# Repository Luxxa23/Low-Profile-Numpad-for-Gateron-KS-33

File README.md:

# Low Profile Numpad

for Gateron Low Profile 2.0 (KS-33) switches
Designed to fit in next to a Keychron K3 Max (or their other low profile keyboards)

## Design Process

The numpd was designed to match the outer dimensions of my Keychron K3 Max and use the same hotswap switches. The PCB was designed in [KiCad](https://github.com/KiCad), the case in Autodesk 
Fusion and the plate in [LibreCad](https://github.com/LibreCAD/LibreCAD) and imported into KiCad.
This was my first time designing a PCB, so the design is probably far from optimal. But it works!

Things to improve/do differently:
- Use the switches with a black housing to blend in with the black case
- Use original Keychron keycaps (if they sold them separately...)

## Building Materials

* Gateron [KS-33 Switches ](https://www.gateron.com/products/gateron-ks-33-low-profile-switch-set)
* Gateron [Low Profile Hotswap Sockets](https://www.gateron.com/products/gateron-low-profile-switch-hot-swap-pcb-socket)
* Gateron [Low Profile Stabilizers](https://www.gateron.com/products/gateron-low-profile-plate-mounted-stabilizer?VariantsId=10477)
* Wormier double-shot PBT keycaps [Aliexpress](https://aliexpress.com/item/1005008227731750.html)

* Adafruit [QT Py RP2040](https://www.adafruit.com/product/4900)
* 0.91" OLED Display (SSD1306) [Aliexpress](https://de.aliexpress.com/item/1005004622658983.html)
* Bourns PEC11R-4315F-S0012 [Encoder](https://www2.mouser.com/ProductDetail/652-PEC11R4315FS0012)
* PCBs ordered on [JLCPCB](https://jlcpcb.com/)
* M2 heat set inserts and screws

## Build Notes

* PCBs ordered on [JLCPCB](https://jlcpcb.com/). The main PCB is 1.6mm thick, the plate PCB is 1mm thick.

* The parts were printed on a BambuLab A1 using their black PLA Basic filament.

* The fit of the PCB is pretty tight, maybe it should've been a few millimetres wider. There are holes for M2x3 heat set inserts in the case. I used black M2x8 screws with a flat, non-countersunk head.
* I used a sharpie to paint the edge of the plate PCB black.
* Use thin, flexible wires for the encoder since there's no a lot of space in the case
*The cover for the OLED is only 0.6mm at the top, so it's very flimsy. If you have a smooth build plate print it upside down, I printed it using the top layer ironing feature with supports. The OLED is supposed to slide into the cover from the side. The fit is too tight, so use a small file to get it to fit perfectly.
*There are 11mm diameter, 1.5mm deep holes on the botton where for small rubber feet can be stuck.

## Firmware

Since the numpad is using an RP2040 processor, I decided to use [KMK Firmware](https://github.com/KMKfw/kmk_firmware).
I uploaded my code.py file, you'll have to install and set up KMK yourself (and edit the OLED display contents/make your own images for it)
My programming knowledge is pretty limited and there aren't a lot of resources on KMK online, so I didn't figure out how to get the display to show Num- and Caps lock without using dummy layers as variables.

## Inspiration and resources

Inspiration for plate PCB and distances between keys: https://github.com/shanna/pla_nck

KiCad footprint for Gateron Low Profile hotswap sockets: https://gist.github.com/niw/22c68c2d7c869b990588b4875a654442 

## Gallery

.jpg)

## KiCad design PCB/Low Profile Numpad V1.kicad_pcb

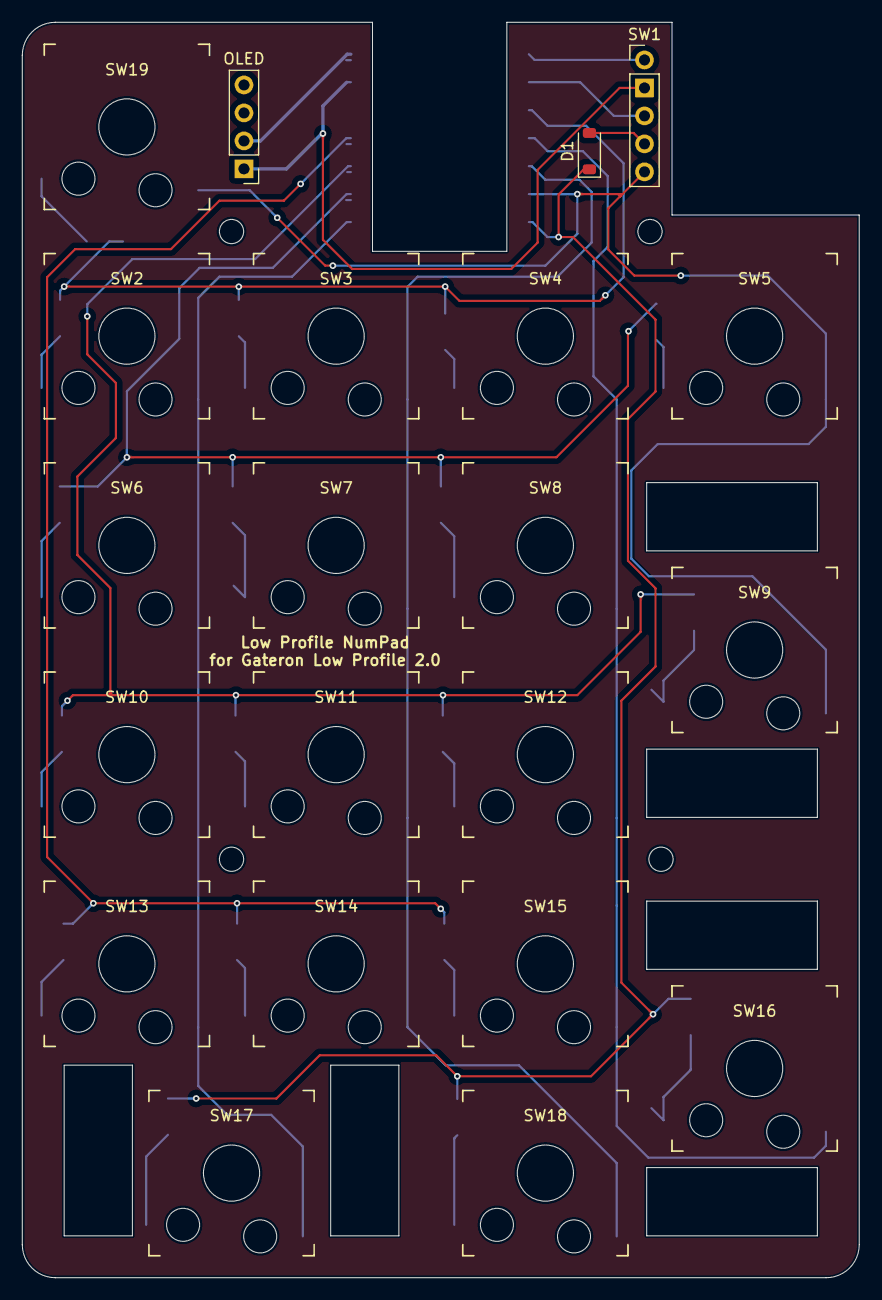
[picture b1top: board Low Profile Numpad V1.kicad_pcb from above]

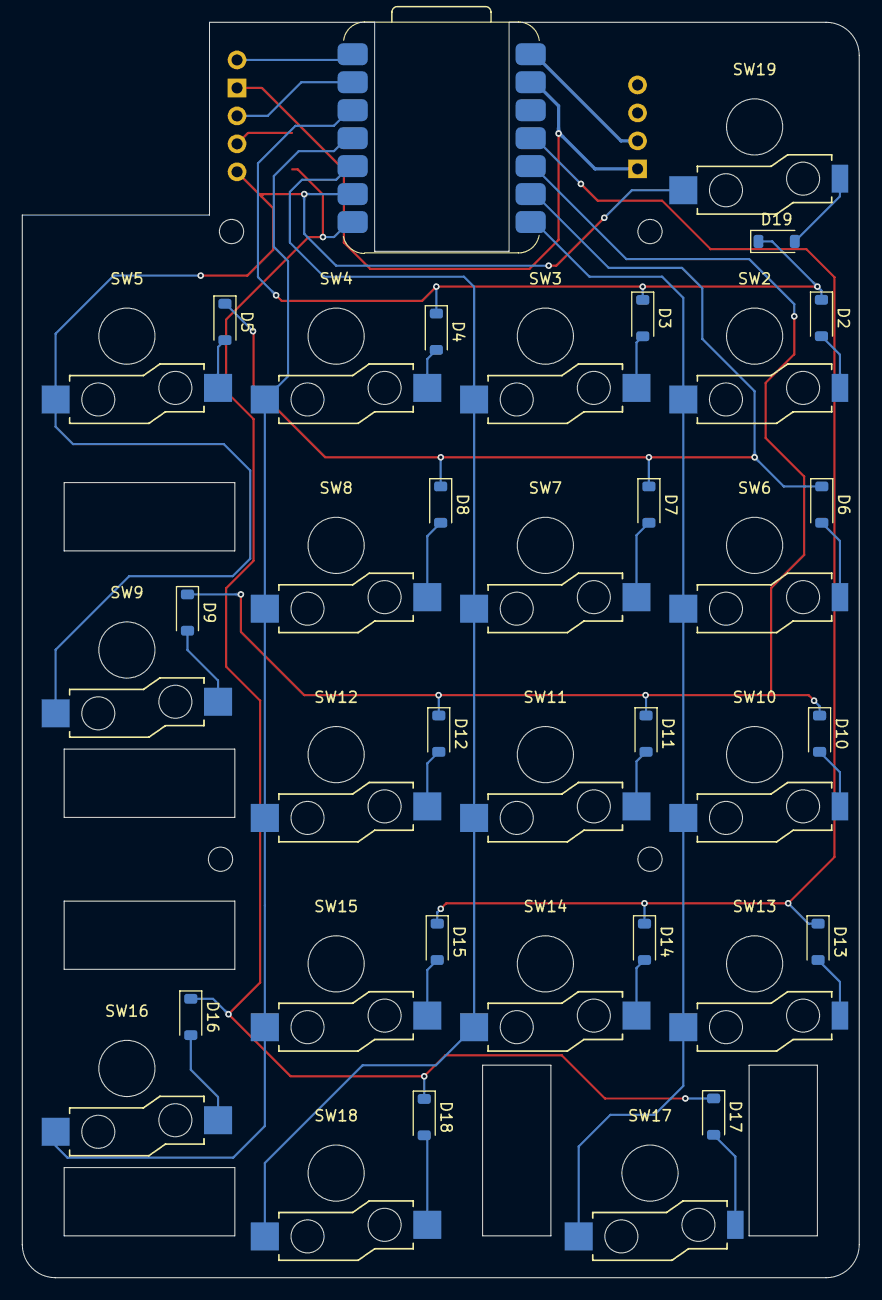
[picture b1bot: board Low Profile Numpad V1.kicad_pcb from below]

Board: 2 copper layers, 76.0 x 114.0 mm, 40 parts (19 on the bottom side), 31 nets.

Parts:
D1, D2, D3, D4, D5, D6, D7, D8, D9, D10, D11, D12, D13, D14, D15, D16, D17, D18, D19: 1N4148W; D_SOD-123
OLED: PinHeader_1x04_P2.54mm_Vertical
SW1: RotaryEncoder_Switch; PinHeader_1x05_P2.54mm_Vertical
SW2, SW6, SW10, SW13, SW19: SW_DPST_x2; Gateron_Low_Profile_Socket (small left pad)
SW3, SW4, SW5, SW7, SW8, SW9, SW11, SW12, SW14, SW15, SW16, SW17, SW18: SW_DPST_x2; Gateron_Low_Profile_Socket
U2: XIAO-RP2040-DIP; Adafrui QT Py RP2040 SMD

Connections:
Column 0: SW2.2 (B), SW6.2 (B), SW10.2 (B), SW13.2 (B), SW17.2 (B), U2.8 (GPIO1/RX)
Column 1: SW3.2 (B), SW7.2 (B), SW11.2 (B), SW14.2 (B), SW18.2 (B), U2.5 (GPIO6/SDA)
Column 2: SW4.2 (B), SW8.2 (B), SW12.2 (B), SW15.2 (B), SW16.2 (B), U2.4 (GPIO29/ADC3/A3)
Column 3: SW1.5, SW5.2 (B), SW9.2 (B), SW19.2 (B), U2.6 (GPIO7/SCL)
GND: OLED.1, SW1.2, U2.13 (GND)
unnamed: D1.2 (A), SW1.4
unnamed: D2.2 (A), SW2.1 (A)
unnamed: D3.2 (A), SW3.1 (A)
unnamed: D4.2 (A), SW4.1 (A)
unnamed: D5.2 (A), SW5.1 (A)
unnamed: D6.2 (A), SW6.1 (A)
unnamed: D7.2 (A), SW7.1 (A)
unnamed: D8.2 (A), SW8.1 (A)
unnamed: D9.2 (A), SW9.1 (A)
unnamed: D10.2 (A), SW10.1 (A)
unnamed: D11.2 (A), SW11.1 (A)
unnamed: D12.2 (A), SW12.1 (A)
unnamed: D13.2 (A), SW13.1 (A)
unnamed: D14.2 (A), SW14.1 (A)
unnamed: D15.2 (A), SW15.1 (A)
unnamed: D16.2 (A), SW16.1 (A)
unnamed: D17.2 (A), SW17.1 (A)
unnamed: D18.2 (A), SW18.1 (A)
unnamed: D19.2 (A), SW19.1 (A)
unnamed: SW1.1, U2.1 (GPIO26/ADC0/A0)
unnamed: SW1.3, U2.2 (GPIO27/ADC1/A1)
Row 0: D2.1 (K), D3.1 (K), D4.1 (K), D19.1 (K), U2.3 (GPIO28/ADC2/A2)
Row 1: D5.1 (K), D6.1 (K), D7.1 (K), D8.1 (K), U2.9 (GPIO2/SCK)
Row 2: D9.1 (K), D10.1 (K), D11.1 (K), D12.1 (K), U2.10 (GPIO4/MISO)
Row 3: D13.1 (K), D14.1 (K), D15.1 (K), U2.11 (GPIO3/MOSI)
Row 4: D1.1 (K), D16.1 (K), D17.1 (K), D18.1 (K), U2.7 (GPIO0/TX)

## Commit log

2025-02-12 Create a
